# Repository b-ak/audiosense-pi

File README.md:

## AudioSense-Pi

**[AudioSense-Pi](https://certification.oshwa.org/in000007.html)** is a RPi HAT based on a TI's stereo codec.  
It is **Open Source Harwdare Association (OSHWA)** certified with **_UID - IN000007_**  

This hardware provides audio input capabilities to the RPi.   
The codec connects to the RPi's SoC through the I2S Bus.

_The codec chosen, allows interfacing **multiple audio I/O** to the RPi._   

**Multiple I/O?** _Yes!_   
The following devices can be connected through a 3.5mm jack
1. Line-In: Plain old audio in from mobile phones, PCs, etc.,
2. Mic-In: Connect a microphone
3. Line-Out: Connect the output to a speaker
4. Headphones: Connect a Headphone w or w/o microphones

**Simultaneous Inputs?** _Yes!_    
It supports the following combinations
1. Two stereo Line-Inputs and a microphone
2. One stereo Line-Input and two microphones
3. Two stereo Line-Inputs, a microphone and one mono line-input (with h/w hack)
4. One stereo Line-Input, two microphones and one mono line-input (with h/w hack)

**Simultaneous Outputs?** _Yes!_   
Audio output can be routed to the headphones or speakers (with additional hardware)

#### Hardware overview       

#### Software overview   
Using the ALSA System on Chip (ASoC) layer we write a machine driver for the HAT.   
With the following changes a new sound card by the name `audiosense-pi` will appear
1. A device tree overlay is added for hardware configuration.
2. Changes to the configuration file (config.txt).
3. ASoC machine driver, makefile and kconfig changes
4. Minimal changes to the ASoC codec driver to handle deprecated APIs

## Getting started with AudioSense-Pi

#### Fab
1. Order the [BOM](./hardware/AudioSense-Pi_BOM.ods)
2. Send the [gerber files](./hardware/audiosense-pi-gerber.zip) to your nearest fab house
3. Assemble the board, it should look something like this..

Assembled Board    

#### Preparing the SD card

We have three ways to setup audiosense
1. Get the [prebuilt images](https://drive.google.com/file/d/10sPdlaTlowZFA2HO4iOQT1hiyIX3uXNR/view?usp=sharing), flash it into a SD card, fly away!
2. Stay with the existing image you have, build the kernel yourself and flash only the kernel image
    * Pull the raspberry pi [kernel source](https://github.com/raspberrypi/linux.git)
    * Use [this](https://github.com/b-ak/helper-scripts/blob/master/rpi3-kernel-builder.sh) script to build and flash the kernel image to the SD card
    * Edit/add the following lines to the `config.txt` in the boot partiton of the SD card
    ```
        # Uncomment some or all of these to enable the optional hardware interfaces
        dtparam=i2c_arm=on
        dtparam=i2s=on
        dtparam=spi=on
        
        # Uncomment this to enable the lirc-rpi module
        #dtoverlay=lirc-rpi
        
        # Additional overlays and parameters are documented /boot/overlays/README
        dtoverlay=audiosense-pi

        # Enable audio (loads snd_bcm2835)
        dtparam=audio=on
    ```    
    * Boot the pi, run the command `aplay -l` you should see a new soundcard `audiosense-pi`
3. Get a kernel image that you want, merge the patches manually, build and flash the kernel image (*for advanced kernel developers*)
    * Clone the kernel sources you want
    * Apply the patches in the [software directory](./software) (`git am` might not work owing to the large number of changes among the trees)
    * Use the script in step 2, apply the `config.txt` changes and boot the pi

#### Configuring the soundcard
1. Open terminal, type in `alsamixer`. Hit `F6` and select `audiosense-pi` from the list of soundcards
	Soundcard selection    
	
2. Soundcard widgets and control settings    
	
3. Plug in an audio-input to the board, a headphones and run `arecord -D hw:1 -c 2 -r 48000 -f S16_LE | aplay -D hw:1`
4. If you did everything right, you will be listening to your favourite song ;)

## License Information  

*Hardware* licensed under the _CERN Open Hardware License version 1.2_   
*Software* licensed under the _GNU GPLv2_   
*Documentation* licensed under _CC0 1.0 Universal_

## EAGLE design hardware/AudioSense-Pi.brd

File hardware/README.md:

## AudioSense-Pi Hardware 

**Schematics**       

**Board**       

**PCB Top**       

**PCB Bottom**       

**Assembly**      

## License Information  

*Hardware* licensed under the _CERN Open Hardware License version 1.2_   
*Software* licensed under the _GNU GPLv2_   
*Documentation* licensed under _CC0 1.0 Universal_

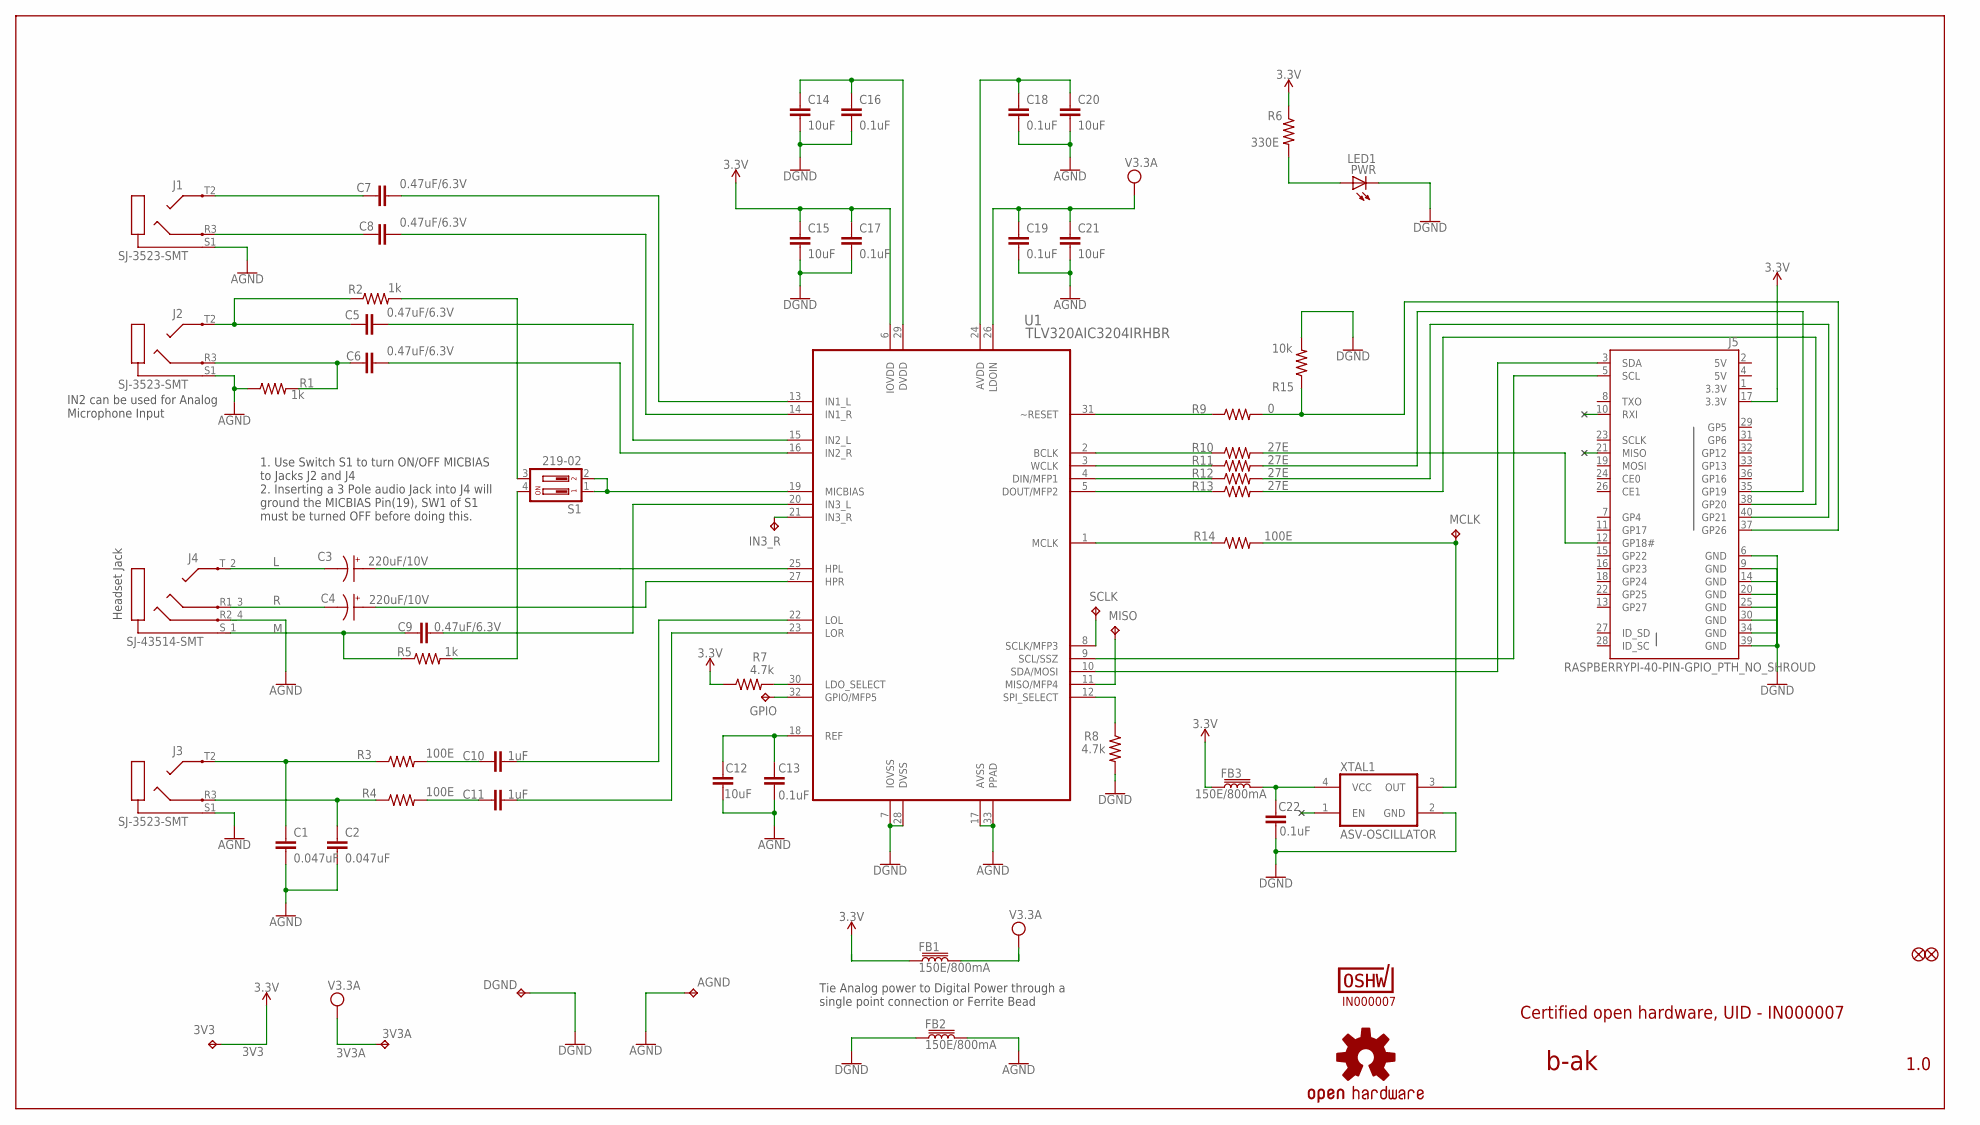
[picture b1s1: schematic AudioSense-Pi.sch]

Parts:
3V3, 3V3A: TPB1,27; B1,27
AGND: TPB1,27; B1,27
C1, C2: 0.047uF; C1206; MANUFACTURER_PART_NUMBER 1206ZC473KAT2A
C3, C4: 220uF/10V; D; MANUFACTURER_PART_NUMBER T491D227K010AT
C5, C6, C7, C8, C9: 0.47uF/6.3V; C1206; MANUFACTURER_PART_NUMBER CC1206KRX7R7BB474
C10, C11: 1uF; C1206; MANUFACTURER_PART_NUMBER CC1206JKX7R7BB105
C12, C14, C15, C20, C21: 10uF; C1206; MANUFACTURER_PART_NUMBER C1206C106J4RACTU
C13, C16, C17, C18, C19, C22: 0.1uF; C1206; MANUFACTURER_PART_NUMBER C1206C104K4RACTU
DGND: TPB1,27; B1,27
FB1, FB2, FB3: 150E/800mA; _0805MP; MANUFACTURER_PART_NUMBER BLM21AG151SN1D
FID1, FID2: FIDUCIAL""; FIDUCIAL_1MM
GPIO: TPB1,27; B1,27
IN3_R: TPB1,27; B1,27
J1, J2, J3: SJ-3523-SMT; MANUFACTURER_PART_NUMBER SJ-3523-SMT-TR
J4: SJ-43514-SMT; MANUFACTURER_PART_NUMBER SJ-43514-SMT-TR
J5: RASPBERRYPI-40-PIN-GPIO_PTH_NO_SHROUD; 2X20; MANUFACTURER_PART_NUMBER 1979
LOGO2: OSHW-LOGOM; OSHW-LOGO-M
MCLK: TPB1,27; B1,27
MISO: TPB1,27; B1,27
PWR: LED1; CHIP-LED0805; MANUFACTURER_PART_NUMBER LTST-C150GKT
R1, R2, R5: 1k; 1206; MANUFACTURER_PART_NUMBER RC1206FR-071KL
R3, R4, R14: 100E; 1206; MANUFACTURER_PART_NUMBER RC1206FR-07100RL
R6: 330E; 1206; MANUFACTURER_PART_NUMBER RC1206JR-07330RL
R7, R8: 4.7k; 1206; MANUFACTURER_PART_NUMBER RC1206FR-074K7L
R9: 0; 1206; MANUFACTURER_PART_NUMBER AC1206JR-070RL
R10, R11, R12, R13: 27E; 1206; MANUFACTURER_PART_NUMBER RC1206JR-0727RL
R15: 10k; 1206; MANUFACTURER_PART_NUMBER RC1206FR-0710KP
S1: 219-02; CTS-219-02
SCLK: TPB1,27; B1,27
U1: TLV320AIC3204IRHBR; QFN50P500X500X100-33N; MANUFACTURER_PART_NUMBER TLV320AIC3204IRHBR
U$6: IN000007; CERT-SMALL-SILK
XTAL1: ASV-OSCILLATOR; OSCILLATOR_7X5_SMD; MANUFACTURER_PART_NUMBER ASV-12.000MHZ-EJ-T

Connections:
3POLE_MBIAS: R2.2, S1.3
3V3: 3V3.TP, C15.1, C17.1, FB1.1, FB3.1, J5.1 (3.3V), J5.17 (3.3V), R6.1, R7.1, U1.6 (IOVDD)
3V3A: 3V3A.TP, C19.1, C21.1, FB1.2, U1.26 (LDOIN)
4POLE_MBIAS: R5.2, S1.4
5V: J5.2 (5V), J5.4 (5V)
AGND: AGND.TP, C1.2, C2.2, C12.2, C13.2, C18.2, C19.2, C20.2, C21.2, FB2.2, J1.S1, J2.S1, J3.S1, J4.R2_4, R1.1, U1.17 (AVSS), U1.33 (PPAD)
AIC_LINE_LOUT_1: C10.1, R3.2
AIC_LINE_ROUT_1: C11.1, R4.2
AVDD: C18.1, C20.1, U1.24 (AVDD)
BCLK: R10.1, U1.2 (BCLK)
DIN: R12.1, U1.4 (DIN/MFP1)
DOUT: R13.1, U1.5 (DOUT/MFP2)
DVDD: C14.1, C16.1, U1.29 (DVDD)
GND: C14.2, C15.2, C16.2, C17.2, C22.2, DGND.TP, FB2.1, J5.6 (GND), J5.9 (GND), J5.14 (GND), J5.20 (GND), J5.25 (GND), J5.30 (GND), J5.34 (GND), J5.39 (GND), PWR.C, R8.2, R15.2, U1.7 (IOVSS), U1.28 (DVSS), XTAL1.2 (GND)
GPIO: GPIO.TP, U1.32 (GPIO/MFP5)
GP_26: J5.37 (GP26), R9.2, R15.1
HPL: C3.+ (A), U1.25 (HPL)
HPR: C4.+ (A), U1.27 (HPR)
IN1L: C7.2, U1.13 (IN1_L)
IN1R: C8.2, U1.14 (IN1_R)
IN1_RING: C8.1, J1.R3
IN1_TIP: C7.1, J1.T2
IN2L: C5.2, U1.15 (IN2_L)
IN2R: C6.2, U1.16 (IN2_R)
IN2_RING: C6.1, J2.R3, R1.2
IN2_TIP: C5.1, J2.T2, R2.1
IN3L: C9.2, U1.20 (IN3_L)
IN3_R: IN3_R.TP, U1.21 (IN3_R)
L: C3.- (C), J4.T_2
LDO_SEL: R7.2, U1.30 (LDO_SELECT)
LED-A: PWR.A, R6.2
LOL: C10.2, U1.22 (LOL)
LOR: C11.2, U1.23 (LOR)
LOUT_RING: C2.1, J3.R3, R4.1
LOUT_TIP: C1.1, J3.T2, R3.1
M: C9.1, J4.S_1, R5.1
MCLK: R14.1, U1.1 (MCLK)
MICBIAS: S1.1, S1.2, U1.19 (MICBIAS)
MISO: MISO.TP, U1.11 (MISO/MFP4)
R: C4.- (C), J4.R1_3
REF: C12.1, C13.1, U1.18 (REF)
RESET: R9.1, U1.31 (~RESET)
RPI_BCLK_PIN12: J5.12 (GP18#), R10.2
RPI_DIN_PIN38: J5.38 (GP20), R13.2
RPI_DOUT_PIN40: J5.40 (GP21), R12.2
RPI_FS_PIN35: J5.35 (GP19), R11.2
SCL: J5.5 (SCL), U1.9 (SCL/SSZ)
SCLK: SCLK.TP, U1.8 (SCLK/MFP3)
SDA: J5.3 (SDA), U1.10 (SDA/MOSI)
SPI_SEL: R8.1, U1.12 (SPI_SELECT)
VCC: C22.1, FB3.2, XTAL1.4 (VCC)
WCLK: R11.1, U1.3 (WCLK)
XTAL_OUT: MCLK.TP, R14.2, XTAL1.3 (OUT)

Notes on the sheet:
Tie Analog power to Digital Power through a single point connection or Ferrite Bead
b-ak
1. Use Switch S1 to turn ON/OFF MICBIAS to Jacks J2 and J4 2. Inserting a 3 Pole audio Jack into J4 will ground the MICBIAS Pin(19), SW1 of S1 must be turned OFF before doing this.
IN2 can be used for Analog Microphone Input
Headset Jack
1.0
Certified open hardware, UID - IN000007

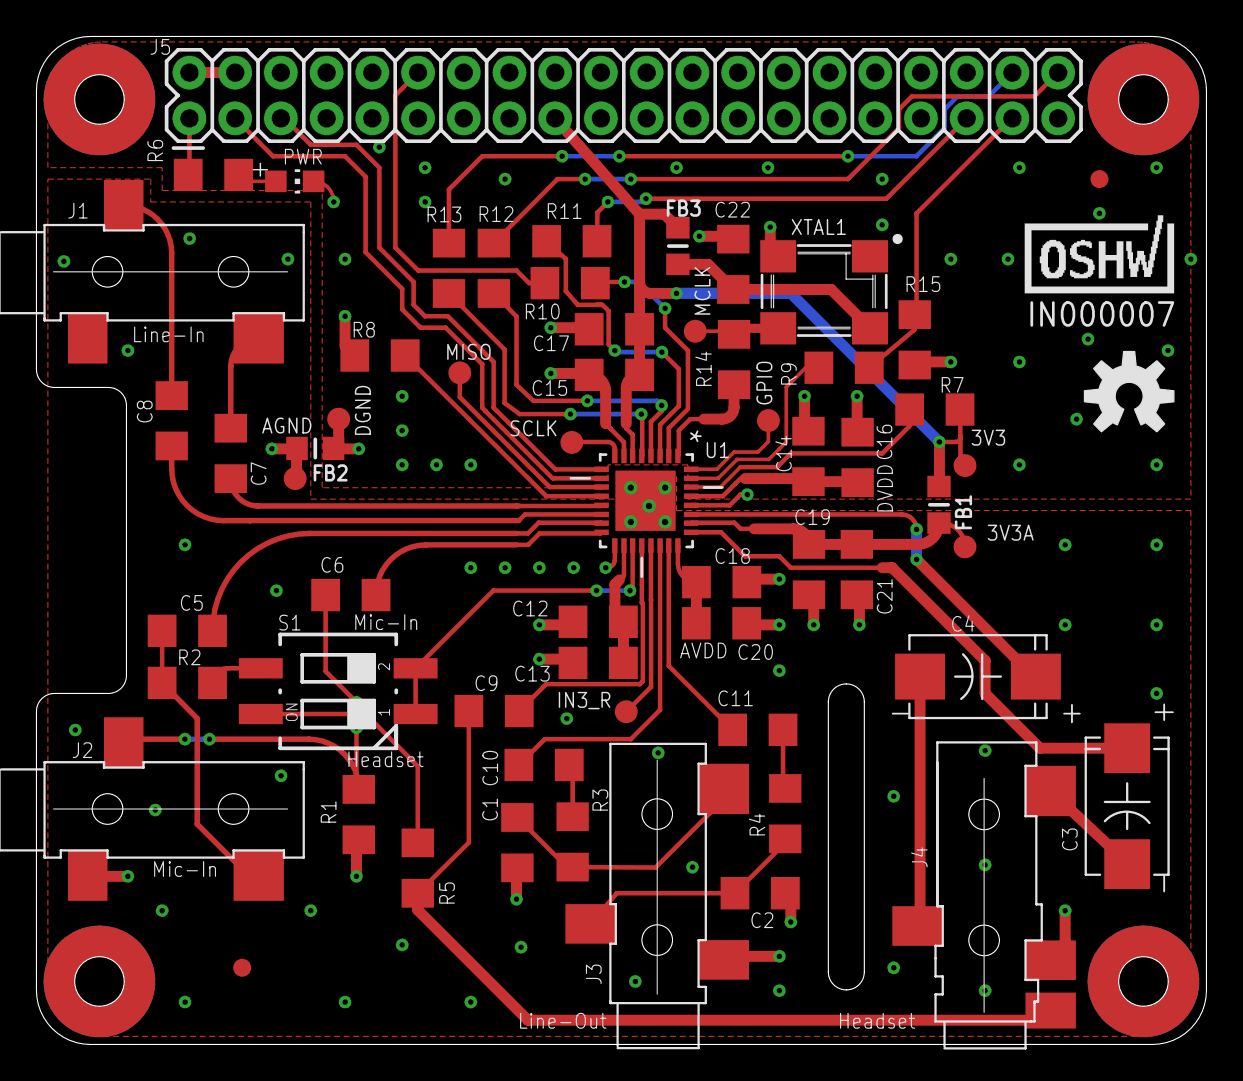
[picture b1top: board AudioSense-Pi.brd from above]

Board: 2 copper layers, 65.0 x 56.0 mm, 62 parts (0 on the bottom side), 53 nets.

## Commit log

2019-08-29 Pushing all OSHW files here
2021-02-09 Update README.md
    Updated links to Prebuilt-Image and build script
2022-01-27 ODS viewer not available in Ubuntu, PDF version of BOM..

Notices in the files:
parts and their libraries:
Volks73-Kemet: Creative Commons Attribution-ShareAlike 3.0 Unported (CC BY-SA 3.0), http://creativecommons.org/licenses/by-sa/3.0/.
SparkFun-Connectors: Licensing: Creative Commons ShareAlike 4.0 International - https://creativecommons.org/licenses/by-sa/4.0
